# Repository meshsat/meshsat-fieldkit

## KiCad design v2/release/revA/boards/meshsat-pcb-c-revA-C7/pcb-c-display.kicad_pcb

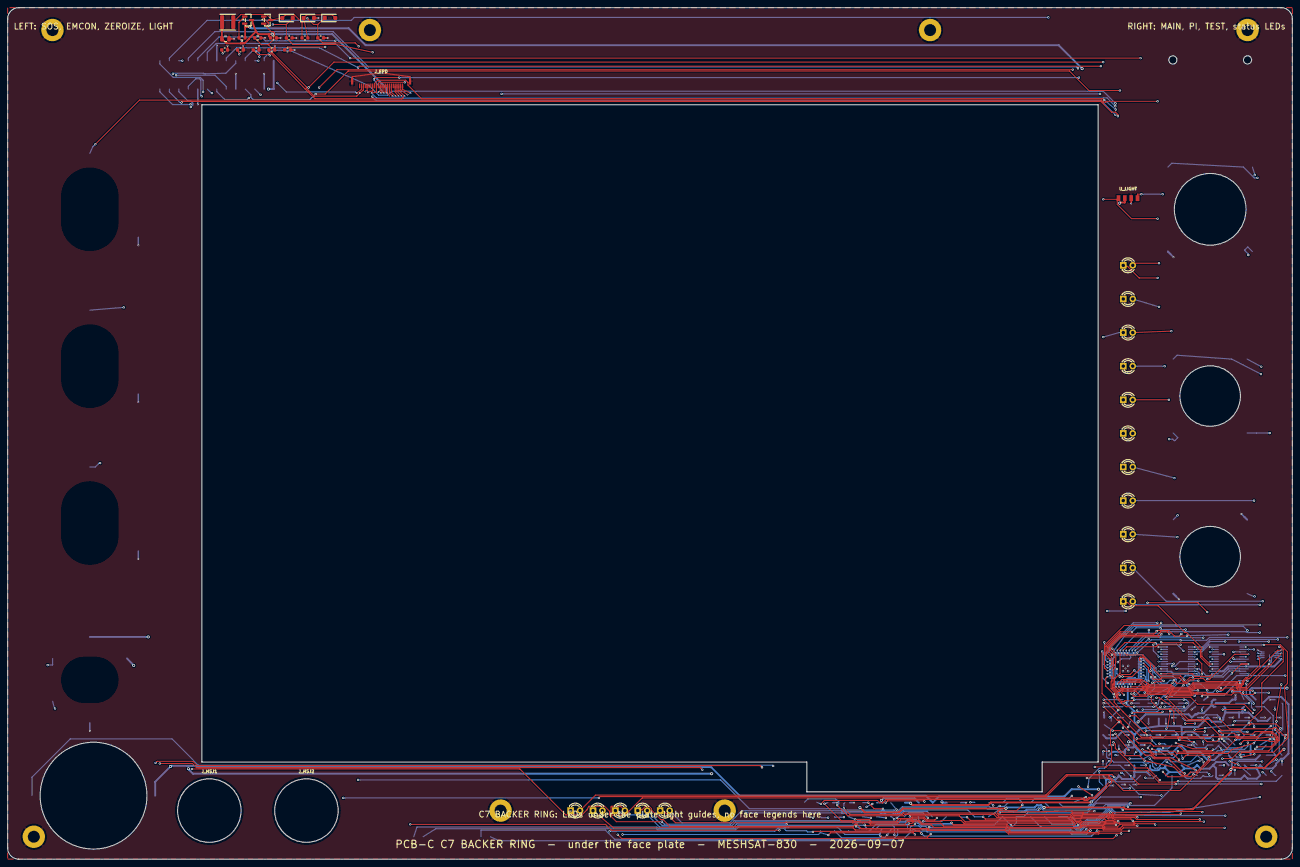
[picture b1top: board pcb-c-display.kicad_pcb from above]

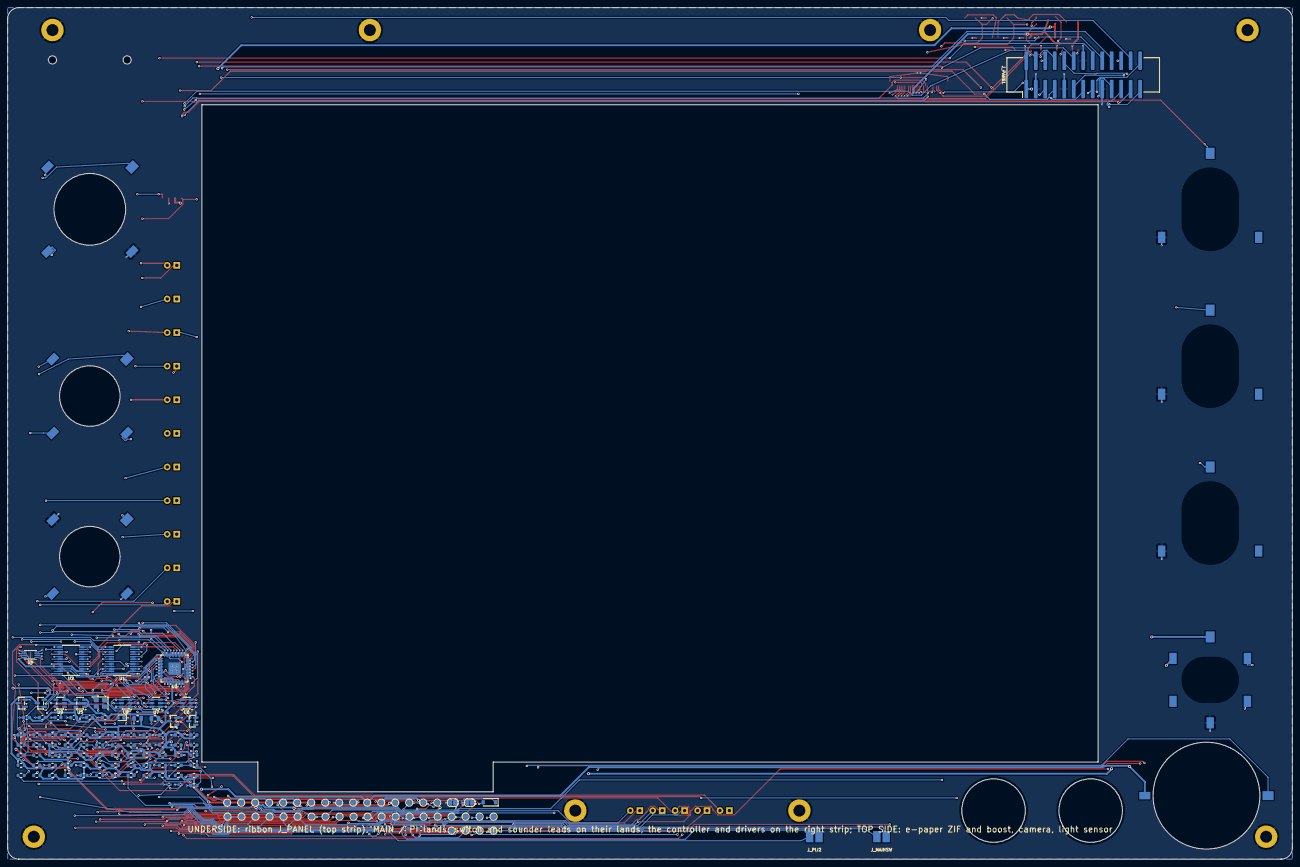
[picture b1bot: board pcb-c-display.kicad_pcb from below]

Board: 4 copper layers, 344.0 x 228.0 mm, 192 parts (136 on the bottom side), 133 nets.

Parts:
BZ1: IP67 panel-mount sounder, 5 V DC continuous, beze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; PanelSounder
C1, C2: 10u; C_0805_2012Metric
C3, C4, C14, C15, C16: 1u; C_0603_1608Metric
C5, C6: 15p NP0; C_0402_1005Metric
C7, C8, C9, C10, C11, C12, C13, C17, C18, C25, C26, C27, C29, C38: 100n; C_0603_1608Metric
C19, C20, C21, C22, C23, C24: 10n; C_0603_1608Metric
C28: 4.7u; C_0805_2012Metric
C30, C31, C32, C33, C34, C35, C36, C37: 1u 25V; C_0603_1608Metric
CAM_H1, CAM_H2: M2 screw of the USB camera module (25 x 25 board,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; MountingHole_2.2mm_M2
D1: 3 mm MWARN red, sunlight viewable; LED_D3.0mm
D2: 3 mm MCAUT amber, sunlight viewable; LED_D3.0mm
D3: 3 mm TX red (RF hazard), sunlight viewable; LED_D3.0mm
D4: 3 mm SOSACT red, sunlight viewable; LED_D3.0mm
D5: 3 mm SAT green, sunlight viewable; LED_D3.0mm
D6: 3 mm MESH green, sunlight viewable; LED_D3.0mm
D7: 3 mm LTE green, sunlight viewable; LED_D3.0mm
D8: 3 mm GPS green, sunlight viewable; LED_D3.0mm
D9: 3 mm SHORE green, sunlight viewable; LED_D3.0mm
D10: 3 mm CHG white, sunlight viewable; LED_D3.0mm
D11: 3 mm MSG white, sunlight viewable; LED_D3.0mm
D12: 3 mm BAT1 amber, sunlight viewable; LED_D3.0mm
D13: 3 mm BAT2 green, sunlight viewable; LED_D3.0mm
D14: 3 mm BAT3 green, sunlight viewable; LED_D3.0mm
D15: 3 mm BAT4 green, sunlight viewable; LED_D3.0mm
D16: 3 mm BAT5 green, sunlight viewable; LED_D3.0mm
D17: BAT54 lamp-test tie; D_SOD-123
D18: status (GPIO25); LED_0603_1608Metric
D19: SS2040FL: EPD_SW -> VGH; D_SOD-123F
D20: SS2040FL: pump clamp; D_SOD-123F
D21: SS2040FL: pump -> VGL; D_SOD-123F
FB1, FB2, FB3, FB4: ferrite 600R; L_0603_1608Metric
H1, H2, H3, H4, H5, H6, H7, H8: M3 x 6 into the face plate's self-clinching stand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; BackerScrew_M3_GND
JP1: BOOTSEL: short while powering to enter the USB bo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; SolderJumper-2_P1.3mm_Open_RoundedPad1.0x1.5mm
JP2: PANEL_ID strap (closed = variant B); SolderJumper-2_P1.3mm_Open_RoundedPad1.0x1.5mm
J_EPD: Hirose FH34SRJ-24S-0.5SH ZIF for the E2370KS0C1 f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; Hirose_FH34SRJ-24S
J_HSJ1: U-174/U headset jack 1 (Amphenol Nexus class, dra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; PanelJack_17mm
J_HSJ2: U-174/U headset jack 2 (Amphenol Nexus class, dra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; PanelJack_17mm
J_MAINSW: MAIN button lead to A22 J_MAINSW (XH2.5 at the A2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; LeadLands_1x02
J_PANEL: panel ribbon from B16 J_PANEL (IDC 2x13 SMD, unde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; IDC-Header_2x13_P2.54mm_Vertical_SMD
J_PIJ2: PI button lead: two solder lands on the underside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; LeadLands_1x02
L1: 10uH ATNR4010100MT 0.8 A (the boost inductor); L_APV_ANR4020
Q1: AO3401A P-FET high side; SOT-23
Q2, Q3, Q4: 2N7002; SOT-23
Q5: AO3401A P-FET: the e-paper's supply switch (EPD_P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; SOT-23
Q6: Si1308EDL class N-FET (RDS under 200 mOhm, VGS 2.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; SOT-23
R1, R6, R37: 1k; R_0603_1608Metric
R2, R3: 27R; R_0603_1608Metric
R4, R9, R10, R11, R12, R13, R15, R16, R42: 10k; R_0603_1608Metric
R5: 1k (BOOTSEL); R_0603_1608Metric
R7, R8, R17: 2.2k; R_0603_1608Metric
R14, R20, R38, R45: 100k; R_0603_1608Metric
R18: 47R; R_0603_1608Metric
R19, R44: 100R; R_0603_1608Metric
R21, R22, R23, R31, R36, R40: 300R; R_0603_1608Metric
R24, R25, R26, R27, R28, R29, R30, R32, R33, R34, R35: 180R; R_0603_1608Metric
R39, R41: 470R; R_0603_1608Metric
R43: 0.47R 1%; R_0603_1608Metric
SW_EMCON: EMCON locking toggle (closed = TX inhibit, a hard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; ToggleBody_SPDT
SW_LIGHT: LIGHTING DAY/NIGHT/BLACKOUT toggle DPDT ON-ON-ON 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; ToggleBody_DPDT
SW_MAIN: MAIN PWR 19 mm momentary, green ring (to A22 J_MA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; PanelSwitch_19mm
SW_PI: PI 16 mm recessed momentary, amber ring (PI_SHDN_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; PanelSwitch_16mm
SW_SOS: SOS locking toggle, maintained (APEM 5636ADKB-2V,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; ToggleBody_SPDT
SW_TEST: TEST/ACK 16 mm momentary, white ring; C&K ATP16-S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; PanelSwitch_16mm
SW_ZERO: ZEROIZE locking toggle, maintained (APEM 5636ADKB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; ToggleBody_SPDT
TP1: SWCLK; TestPoint_Pad_D1.5mm
TP2: SWDIO; TestPoint_Pad_D1.5mm
TP3: C_RUN; TestPoint_Pad_D1.5mm
TP4: LED_RAIL; TestPoint_Pad_D1.5mm
TP5: LED_RAIL_SW; TestPoint_Pad_D1.5mm
TP6: +5V; TestPoint_Pad_D1.5mm
TP7: +3V3; TestPoint_Pad_D1.5mm
TP8: GND; TestPoint_Pad_D1.5mm
TP9: EXP_INT; TestPoint_Pad_D1.5mm
TP10: TX_INHIBIT_n; TestPoint_Pad_D1.5mm
TP11: EMCON_HW; TestPoint_Pad_D1.5mm
TP12: ZEROIZE_HW; TestPoint_Pad_D1.5mm
TP13: SPARE1; TestPoint_Pad_D1.5mm
TP14: SPARE2; TestPoint_Pad_D1.5mm
TP15: SPARE3; TestPoint_Pad_D1.5mm
TP16: SPARE4; TestPoint_Pad_D1.5mm
TP17: SPARE5; TestPoint_Pad_D1.5mm
TP18: SPARE6; TestPoint_Pad_D1.5mm
TP19: SPARE7; TestPoint_Pad_D1.5mm
TP20: SPARE8; TestPoint_Pad_D1.5mm
TP21: SPARE9; TestPoint_Pad_D1.5mm
TP22: SPARE10; TestPoint_Pad_D1.5mm
TP23: SPARE11; TestPoint_Pad_D1.5mm
TP24: SPARE12; TestPoint_Pad_D1.5mm
TP25: EPD_BUSY; TestPoint_Pad_D1.5mm
TP26: EPD_VGH; TestPoint_Pad_D1.5mm
TP27: EPD_VGL; TestPoint_Pad_D1.5mm
TP28: HB1; TestPoint_Pad_D1.5mm
TP29: HB2; TestPoint_Pad_D1.5mm
TP30: HB3; TestPoint_Pad_D1.5mm
TP31: SLOT_EN1; TestPoint_Pad_D1.5mm
TP32: SLOT_EN2; TestPoint_Pad_D1.5mm
TP33: SLOT_EN3; TestPoint_Pad_D1.5mm
TP34: HDMI_SEL1; TestPoint_Pad_D1.5mm
TP35: HDMI_SEL2; TestPoint_Pad_D1.5mm
TP36: PI_SHDN_REQ; TestPoint_Pad_D1.5mm
TP37: PI_KILL; TestPoint_Pad_D1.5mm
TP38: SHORE_INHIBIT; TestPoint_Pad_D1.5mm
TP39: PIJ2_A; TestPoint_Pad_D1.5mm
TP40: PIJ2_B; TestPoint_Pad_D1.5mm
U1: PCA9555PW 0x22: LED sinks, light mode inputs; TSSOP-24_4.4x7.8mm_P0.65mm
U2: PCA9555PW 0x23: LED sinks, the battery bar, lamp 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; TSSOP-24_4.4x7.8mm_P0.65mm
U3: RP2040 panel controller (USB device on B16's slot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; QFN-56-1EP_7x7mm_P0.4mm_EP3.2x3.2mm
U4: W25Q16JVUXIQ 16 Mbit QSPI flash (USON-8: 1 CS 2 D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; Winbond_USON-8-1EP_3x2mm_P0.5mm_EP0.2x1.6mm
U5: TLV75533PDBV 3.3 V 500 mA LDO for the controller,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; SOT-23-5
U6, U7, U8: USBLC6-2SC6; SOT-23-6
U9: 74LVC1G04 inverter (2 A 4 Y): EMCON_HW = NOT TX_I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; SOT-23-5
U_LIGHT: Vishay VEML7700 ambient light sensor (1 SCL 2 VDD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; Vishay_VEML7700
Y1: 12 MHz ABM8-272-T3 (3225): 1 XIN, 3 XOUT, 2 and 4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; Crystal_SMD_3225-4Pin_3.2x2.5mm

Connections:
/+3V3: C2.1, C4.1, C7.1, C8.1, C9.1, C10.1, C11.1, C12.1, C13.1, C16.1, C17.1, C18.1, C25.1, C38.1, Q5.2, R4.2, R7.2, R8.2, R9.2, R10.2, R11.2, R12.2, R13.2, R14.2, R16.2, R42.2, TP7.1, U1.2, U1.24, U2.2, U2.21, U2.24, U3.1, U3.10, U3.22, U3.33, U3.42, U3.43, U3.44, U3.48, U3.49, U4.8, U5.5, U6.5, U7.5, U8.5, U9.5, U_LIGHT.2
/+5V: BZ1.2, C1.1, C3.1, J_PANEL.1, J_PANEL.2, SW_LIGHT.2, TP6.1, U5.1, U5.3
/BAT1_A: D12.2, R31.2
/BAT1_K: D12.1, U2.7
/BAT2_A: D13.2, R32.2
/BAT2_K: D13.1, U2.8
/BAT3_A: D14.2, R33.2
/BAT3_K: D14.1, U2.9
/BAT4_A: D15.2, R34.2
/BAT4_K: D15.1, U2.10
/BAT5_A: D16.2, R35.2
/BAT5_K: D16.1, U2.11
/BOOT_J: JP1.1, R5.2
/BZ_K: BZ1.1, Q4.3
/CHG_A: D10.2, R29.2
/CHG_K: D10.1, U1.7
/C_DVDD: C14.1, C15.1, U3.23, U3.45, U3.50
/C_RUN: R4.1, TP3.1, U3.26
/EMCON_HW: J_PANEL.8, TP11.1, U3.32, U9.4
/EPD_BUSY: J_EPD.9, TP25.1, U3.9
/EPD_CS: J_EPD.12, U3.7
/EPD_DC: J_EPD.11, U3.6
/EPD_GDR: J_EPD.2, Q6.1
/EPD_PUMP: C31.2, D20.1, D21.2
/EPD_PWR_n: Q5.1, R42.1, U3.41
/EPD_RESE: J_EPD.3, Q6.2, R43.1
/EPD_RST: J_EPD.10, U3.8
/EPD_SCL: J_EPD.13, U3.4
/EPD_SDA: J_EPD.14, U3.5
/EPD_SW: C31.1, D19.1, L1.2, Q6.3
/EPD_VCC: C28.1, C29.1, J_EPD.15, J_EPD.16, L1.1, Q5.3
/EPD_VCOM: C37.1, J_EPD.24
/EPD_VDDD: C34.1, J_EPD.18
/EPD_VDH: C35.1, J_EPD.20
/EPD_VDHR: C33.1, J_EPD.5
/EPD_VDL: C36.1, J_EPD.22
/EPD_VGH: C30.1, D19.2, J_EPD.21, TP26.1
/EPD_VGL: C32.1, D21.1, J_EPD.23, TP27.1
/EXP_INT: J_PANEL.6, TP9.1, U1.1, U2.1, U3.36, U8.3, U8.4
/GPS_A: D8.2, R27.2
/GPS_K: D8.1, U1.11
/HB1: J_PANEL.18, TP28.1, U3.13
/HB2: J_PANEL.19, TP29.1, U3.14
/HB3: J_PANEL.20, TP30.1, U3.15
/HDMI_SEL1: J_PANEL.12, TP34.1, U3.27
/HDMI_SEL2: J_PANEL.13, TP35.1, U3.28
/LED_RAIL: Q1.3, R21.1, R22.1, R23.1, R24.1, R25.1, R26.1, R27.1, R28.1, R29.1, R30.1, R31.1, R32.1, R33.1, R34.1, R35.1, R36.1, R40.1, R41.1, TP4.1
/LED_RAIL_SW: Q1.2, R15.1, R17.1, R39.1, SW_LIGHT.1, TP5.1
/LED_STAT: R6.1, U3.37
/LED_STAT_A: D18.2, R6.2
/LIGHT_DAY_n: C22.1, R12.1, SW_LIGHT.5, U1.13
/LIGHT_NIGHT_n: C23.1, R13.1, SW_LIGHT.6, U1.14
/LTE_A: D7.2, R26.2
/LTE_K: D7.1, U1.10
/MAINRING_A: R39.2, SW_MAIN.3
/MAINSW_A: FB1.1, SW_MAIN.1
/MAINSW_A2: C26.1, FB1.2, J_MAINSW.1
/MAINSW_B: FB2.1, SW_MAIN.2
/MAINSW_B2: C26.2, FB2.2, J_MAINSW.2
/MCAUT_A: D2.2, R22.2
/MCAUT_K: D2.1, U1.6
/MESH_A: D6.2, R25.2
/MESH_K: D6.1, U1.9
/MSG_A: D11.2, R30.2
/MSG_K: D11.1, U2.5
/MWARN_A: D1.2, R21.2
/MWARN_K: D1.1, U1.5
/PANEL_ID: JP2.1, R16.1, U1.15
/PANEL_PWM: R19.1, U3.11
/PIJ2_A: FB3.1, SW_PI.1, TP39.1
/PIJ2_A2: C27.1, FB3.2, J_PIJ2.1
/PIJ2_B: FB4.1, SW_PI.2, TP40.1
/PIJ2_B2: C27.2, FB4.2, J_PIJ2.2
/PIRING_A: R40.2, SW_PI.3
/PIRING_K: SW_PI.4, U2.6
/PI_KILL: J_PANEL.25, TP37.1, U3.30
/PI_SHDN_REQ: J_PANEL.24, TP36.1, U3.29
/PWM1: R44.1, U3.12
/Q1_G: Q1.1, R17.2, R18.1
/Q2_D: Q2.3, R18.2
/Q2_G: Q2.1, R19.2, R20.1
/Q3_G: Q3.1, R37.2, R38.1
/Q4_G: Q4.1, R44.2, R45.1
/QSPI_D0: U3.53, U4.5
/QSPI_D1: U3.55, U4.2
/QSPI_D2: U3.54, U4.3
/QSPI_D3: U3.51, U4.7
/QSPI_SCLK: U3.52, U4.6
/QSPI_SS: R5.1, U3.56, U4.1
/RAIL_SENSE: R15.2, U3.38
/SAT_A: D5.2, R24.2
/SAT_K: D5.1, U1.8
/SCL: J_PANEL.5, R8.1, U1.22, U2.22, U3.3, U7.3, U7.4, U_LIGHT.1
/SDA: J_PANEL.4, R7.1, U1.23, U2.23, U3.2, U7.1, U7.6, U_LIGHT.4
/SHORE_A: D9.2, R28.2
/SHORE_INHIBIT: J_PANEL.26, TP38.1, U3.31
/SHORE_K: D9.1, U2.4
/SLOT_EN1: J_PANEL.21, TP31.1, U3.16
/SLOT_EN2: J_PANEL.22, TP32.1, U3.17
/SLOT_EN3: J_PANEL.23, TP33.1, U3.18
/SOSACT_A: D4.2, R23.2
/SOSACT_K: D4.1, U1.4
/SOS_SW: C19.1, R9.1, SW_SOS.1, U3.40
/SPARE1: TP13.1, U1.16
/SPARE2: TP14.1, U1.17
/SPARE3: TP15.1, U1.18
/SPARE4: TP16.1, U1.19
/SPARE5: TP17.1, U1.20
/SPARE6: TP18.1, U2.14
/SPARE7: TP19.1, U2.15
/SPARE8: TP20.1, U2.16
/SPARE9: TP21.1, U2.17
/SPARE10: TP22.1, U2.18
/SPARE11: TP23.1, U2.19
/SPARE12: TP24.1, U2.20
/SWCLK: TP1.1, U3.24
/SWDIO: TP2.1, U3.25
/TESTRING_A: R41.2, SW_TEST.3
/TEST_SW: C21.1, R11.1, SW_TEST.1, U3.39
/TR_APRS: J_PANEL.7, R37.1, U3.35, U8.1, U8.6
/TX_A: D3.2, R36.2
/TX_INHIBIT_n: C24.1, J_PANEL.11, R14.1, SW_EMCON.1, TP10.1, U9.2
/TX_K: D3.1, D17.2, Q3.3
/TX_LAMPTEST: D17.1, U2.13
/USB_DM_R: R3.1, U3.46
/USB_DP_R: R2.1, U3.47
/USB_PNL_N: J_PANEL.16, R3.2, U6.3, U6.4
/USB_PNL_P: J_PANEL.15, R2.2, U6.1, U6.6
/XIN: C5.1, U3.20, Y1.1
/XOUT: C6.1, R1.2, Y1.3
/XOUT_R: R1.1, U3.21
/ZEROIZE_HW: C20.1, J_PANEL.10, R10.1, SW_ZERO.1, TP12.1, U3.34
GND: C1.2, C2.2, C3.2, C4.2, C5.2, C6.2, C7.2, C8.2, C9.2, C10.2, C11.2, C12.2, C13.2, C14.2, C15.2, C16.2, C17.2, C18.2, C19.2, C20.2, C21.2, C22.2, C23.2, C24.2, C25.2, C28.2, C29.2, C30.2, C32.2, C33.2, C34.2, C35.2, C36.2, C37.2, C38.2, D18.1, D20.2, H1.1, H2.1, H3.1, H4.1, H5.1, H6.1, H7.1, H8.1, JP1.2, JP2.2, J_EPD.8, J_EPD.17, J_EPD.25, J_EPD.26, J_PANEL.3, J_PANEL.9, J_PANEL.14, J_PANEL.17, Q2.2, Q3.2, Q4.2, R20.2, R38.2, R43.2, R45.2, SW_EMCON.2, SW_LIGHT.4, SW_MAIN.4, SW_SOS.2, SW_TEST.2, SW_TEST.4, SW_ZERO.2, TP8.1, U1.3, U1.12, U1.21, U2.3, U2.12, U3.19, U3.57, U4.4, U4.9, U5.2, U6.2, U7.2, U8.2, U9.3, U_LIGHT.3, Y1.2, Y1.4

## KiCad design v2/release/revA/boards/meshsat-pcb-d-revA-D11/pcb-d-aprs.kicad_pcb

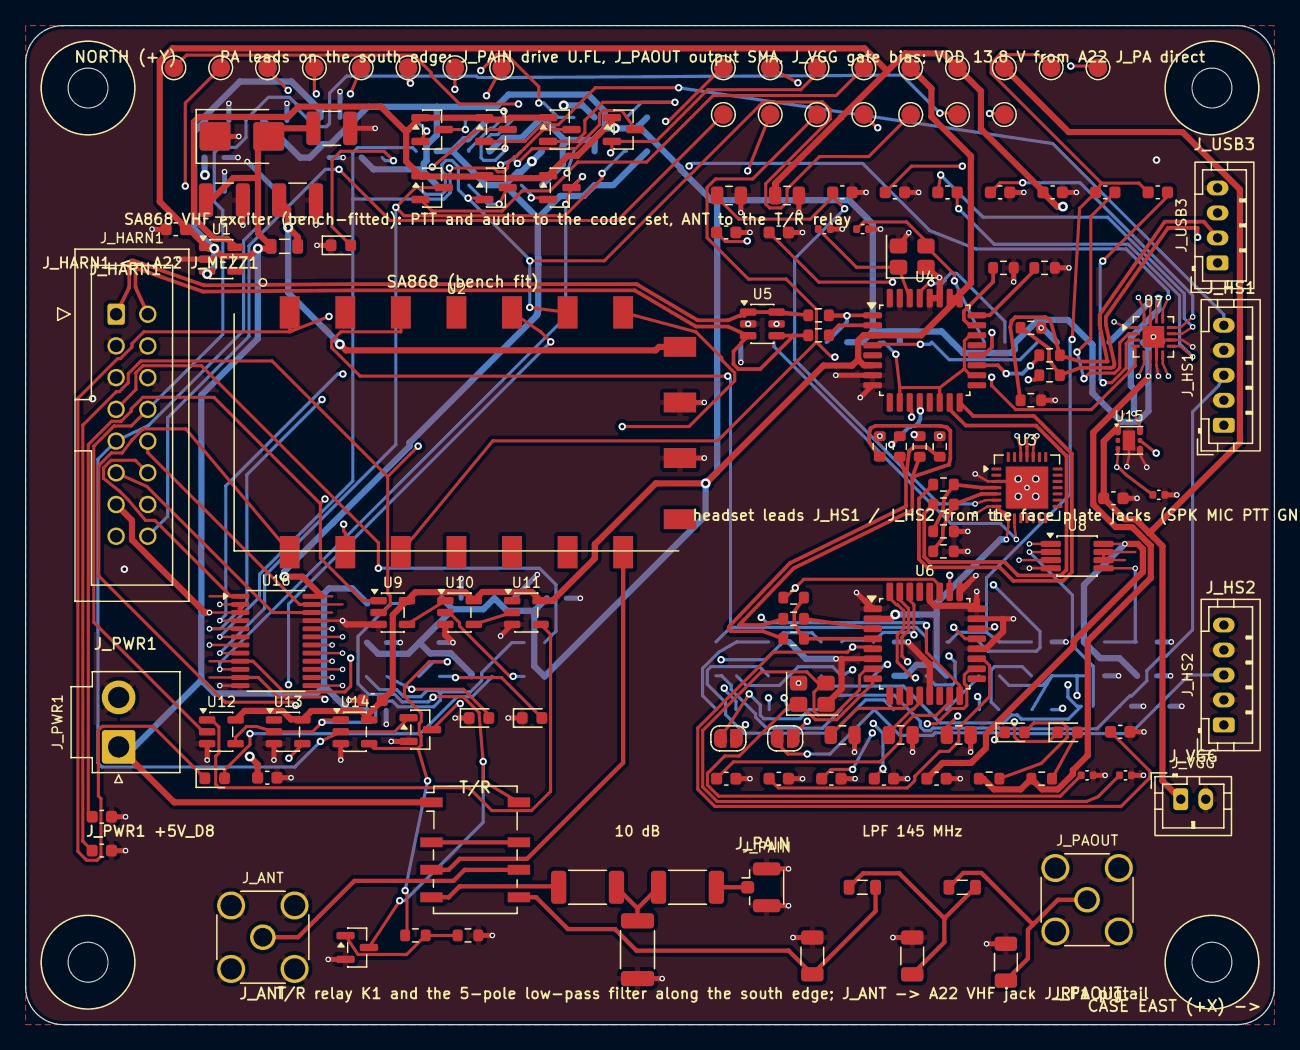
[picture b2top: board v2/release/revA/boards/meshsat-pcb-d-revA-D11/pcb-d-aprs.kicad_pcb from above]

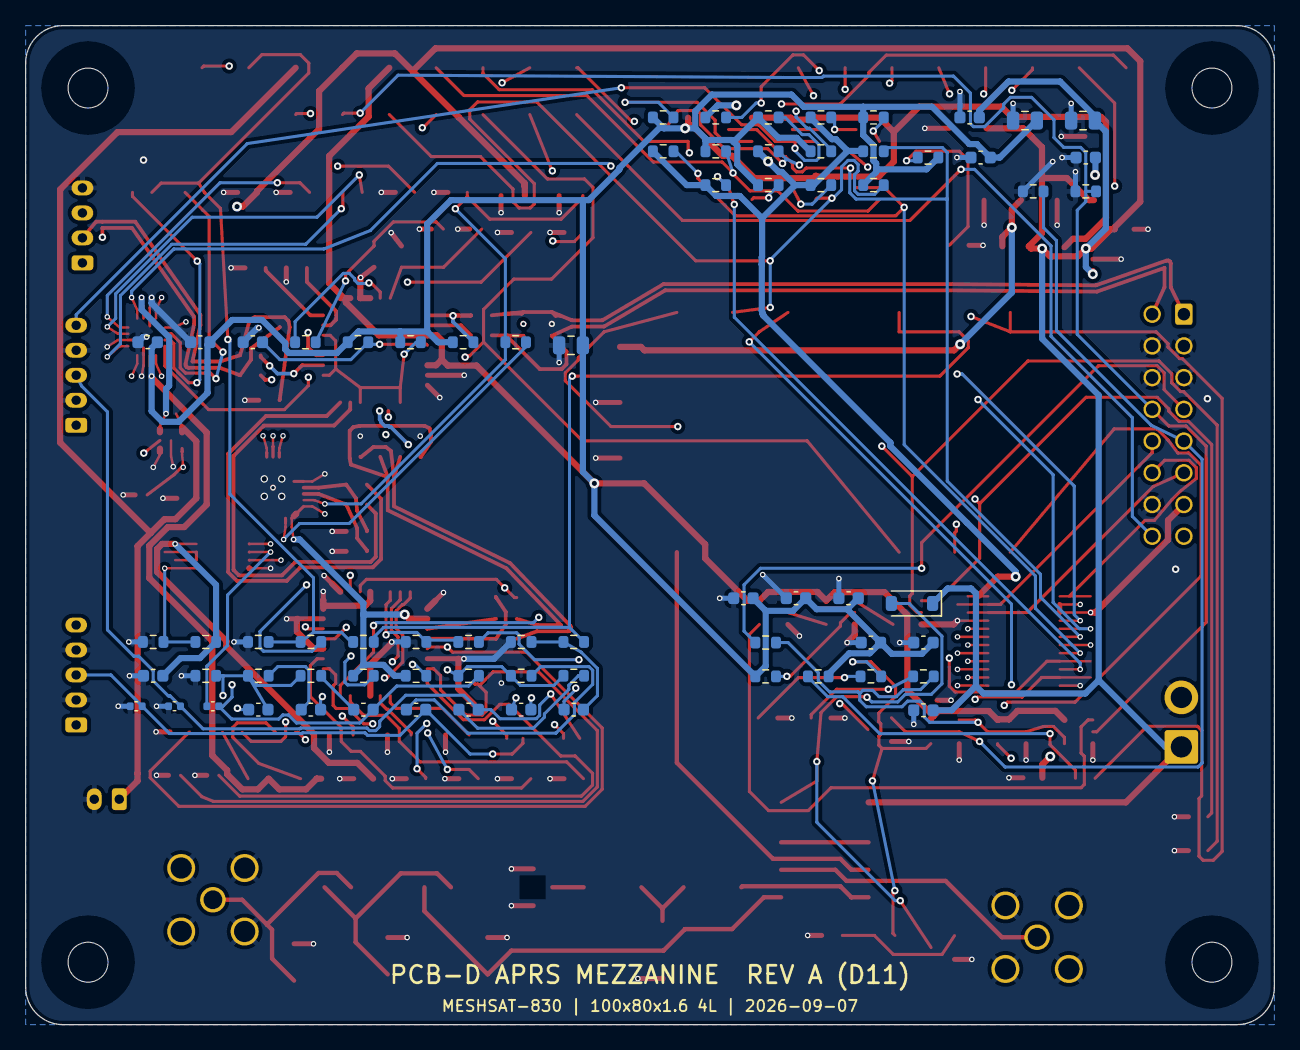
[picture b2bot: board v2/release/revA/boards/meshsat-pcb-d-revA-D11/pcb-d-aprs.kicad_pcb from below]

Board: 4 copper layers, 100.0 x 80.0 mm, 211 parts (71 on the bottom side), 133 nets.

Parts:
C1, C2, C5: 47u 6.3V X5R 1210; C_1210_3225Metric
C3, C9, C17, C24, C25, C33, C40: 10u; C_0805_2012Metric
C4, C6, C11, C15, C16, C39, C49, C50, C51, C52, C53, C54, C55, C56, C57, C62, C63: 100n; C_0603_1608Metric
C7, C8, C12, C18, C19, C20, C21, C22, C23, C28, C29, C30, C31, C32, C34, C35, C36, C37, C38, C41, C42, C46, C47, C48: 1u; C_0603_1608Metric
C10: 4.7u; C_0805_2012Metric
C13, C14: 27p NP0; C_0402_1005Metric
C26, C27: 18p NP0; C_0402_1005Metric
C43: 100p NP0; C_0402_1005Metric
C44, C45: 1n NP0; C_0402_1005Metric
C58, C60: 22p 500V NP0 1206; C_1206_3216Metric
C59: 39p 500V NP0 1206; C_1206_3216Metric
C61: 4.7n; C_0402_1005Metric
D1: SMBJ5.0A; D_SMB
D2: 1N4148W coil flyback; D_SOD-123
FB1: 600R 2A ferrite (the exciter's 1 A transmit pulse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; L_0805_2012Metric
H1, H2, H3, H4: M3 standoff on A22 (5/95, +-35); MountingHole_3.2mm_M3
JP1: electret bias headset 1 (close for an electret mi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; SolderJumper-2_P1.3mm_Open_RoundedPad1.0x1.5mm
JP2: electret bias headset 2; SolderJumper-2_P1.3mm_Open_RoundedPad1.0x1.5mm
J_ANT: SMA jack: antenna pigtail to A22's VHF jack J_RF1; SMA_Amphenol_132134_Vertical
J_HARN1: A22 mezzanine harness J_MEZZ1 (IDC 2x8): USB pair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; IDC-Header_2x08_P2.54mm_Vertical_NarrowPad
J_HS1: JST-PH 1x5 socket: headset 1, SPK GND MIC GND PTT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; JST_PH_B5B-PH-K_1x05_P2.00mm_Vertical
J_HS2: JST-PH 1x5 socket: headset 2, SPK GND MIC GND PTT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; JST_PH_B5B-PH-K_1x05_P2.00mm_Vertical
J_PAIN: U.FL socket: PA drive (coax to the RA30H1317M1 in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; U.FL_Hirose_U.FL-R-SMT-1_Vertical
J_PAOUT: SMA jack: PA output (coax from the RA30H1317M1 ou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; SMA_Amphenol_132134_Vertical
J_PWR1: JST-VH socket, 10 A: 5 V from A22 J_MEZZ_PWR1 (be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; JST_VH_B2P-VH_1x02_P3.96mm_Vertical
J_USB3: JST-PH 1x4 socket: spare hub port 3, 5V D- D+ GND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; JST_PH_B4B-PH-K_1x04_P2.00mm_Vertical
J_VGG: JST-PH 1x2 socket: PA gate bias, VGG GND (the lea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; JST_PH_B2B-PH-K_1x02_P2.00mm_Vertical
K1: Omron G6K-2F-Y 5 VDC DPDT signal relay, T/R; Relay_DPDT_Omron_G6K-2F-Y
L1: 68nH 0805 (LPF, 145 MHz 5th order; values to be v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; L_0805_2012Metric
L2: 68nH 0805 (LPF); L_0805_2012Metric
LED1: green power; LED_0603_1608Metric
LED2: amber record; LED_0603_1608Metric
LED3: green playback; LED_0603_1608Metric
LED4: red transmit; LED_0603_1608Metric
LED5: amber PA keyed; LED_0603_1608Metric
LED6: green receive (AUDIO_ON low); LED_0603_1608Metric
Q1: 2N7002 PA_EN -> H/L low (never tie H/L high); SOT-23
Q2: 2N7002 relay coil; SOT-23
Q3, Q4, Q5, Q6, Q7, Q8, Q9: 2N7002; SOT-23
R1, R43, R44, R51: 2.2k; R_0603_1608Metric
R2, R3, R34, R53: 100k; R_0603_1608Metric
R4, R29, R30, R49, R50, R52: 1k; R_0603_1608Metric
R5, R9, R10, R31, R32, R35, R36, R37, R38, R39, R45, R46, R47, R66, R67, R68, R69, R70, R71, R72, R73, R74, R75, R76, R77, R78, R79: 10k; R_0603_1608Metric
R6, R7, R12, R13, R16, R17, R20, R21: 22; R_0603_1608Metric
R8, R11, R28: 1.5k; R_0603_1608Metric
R14, R15, R18, R19, R22, R23, R24, R25: 15k; R_0603_1608Metric
R26, R27: 33; R_0603_1608Metric
R33, R40, R41: 4.7k; R_0603_1608Metric
R42: 220k; R_0603_1608Metric
R48: 100; R_0603_1608Metric
R54, R56: 27 1% 2010; R_2010_5025Metric
R55: 36 1% 2010; R_2010_5025Metric
TP1: AF_OUT; TestPoint_Pad_D1.5mm
TP2: MIC_SUM; TestPoint_Pad_D1.5mm
TP3: KEY; TestPoint_Pad_D1.5mm
TP4: PA_KEY; TestPoint_Pad_D1.5mm
TP5: +3V3_D8; TestPoint_Pad_D1.5mm
TP6: +5V_D8; TestPoint_Pad_D1.5mm
TP7: VGG_SW; TestPoint_Pad_D1.5mm
TP8: RX_MIX; TestPoint_Pad_D1.5mm
TP9: ZEROIZE_HW; TestPoint_Pad_D1.5mm
TP10: AB_SPARE; TestPoint_Pad_D1.5mm
TP11: SA_TXD; TestPoint_Pad_D1.5mm
TP12: SA_RXD; TestPoint_Pad_D1.5mm
TP13: PTT_SW_n; TestPoint_Pad_D1.5mm
TP14: SA_PD; TestPoint_Pad_D1.5mm
TP15: TX_INHIBIT_n; TestPoint_Pad_D1.5mm
TP16: PA_EN; TestPoint_Pad_D1.5mm
TP17: EXP_SPARE1; TestPoint_Pad_D1.5mm
TP18: EXP_SPARE2; TestPoint_Pad_D1.5mm
TP19: EXP_SPARE3; TestPoint_Pad_D1.5mm
TP20: EXP_SPARE4; TestPoint_Pad_D1.5mm
TP21: EXP_SPARE5; TestPoint_Pad_D1.5mm
TP22: EXP_SPARE6; TestPoint_Pad_D1.5mm
TP23: EXP_SPARE7; TestPoint_Pad_D1.5mm
TP24: EXP_SPARE8; TestPoint_Pad_D1.5mm
U1: TLV75533PDBV 3.3 V 500 mA LDO (1 IN 2 GND 3 EN 4 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; SOT-23-5
U2: NiceRF SA868 VHF 2 W exciter, bench-fitted (caste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; NiceRF_SA868
U3: CP2102N-A02-GQFN28 USB-UART bridge (SAU); QFN-28-1EP_5x5mm_P0.5mm_EP3.35x3.35mm
U4: TUSB2046BI four-port USB 2.0 full-speed hub (LQFP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; LQFP-32_7x7mm_P0.8mm
U5: USBLC6-2SC6; SOT-23-6
U6: TI PCM2912A USB audio codec (TQFP-32): mono input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; TQFP-32_7x7mm_P0.8mm
U7: TI TPA6132A2 headphone amplifier (QFN-16), receiv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; QFN-16-1EP_3x3mm_P0.5mm_EP1.75x1.75mm
U8: TLV9062IDGK dual op amp (1 OUT1 2 IN1- 3 IN1+ 4 V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; VSSOP-8_3x3mm_P0.65mm
U9: 74LVC1G08 AND (1 A 2 B 3 GND 4 Y 5 VCC): both hea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; SOT-23-5
U10: 74LVC1G08 AND: headsets AND software PTT (RTS); SOT-23-5
U11: 74LVC1G04 inverter (2 A 4 Y): PTT_ANY; SOT-23-5
U12: 74LVC1G08 AND: KEY = PTT_ANY AND TX_INHIBIT_n (th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; SOT-23-5
U13: 74LVC1G04 inverter: KEY -> SA868 PTT (low = trans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; SOT-23-5
U14: 74LVC1G08 AND: PA_KEY = KEY AND PA_EN (A22's PA r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; SOT-23-5
U15: TPS22810DRV; WSON-6-1EP_2x2mm_P0.65mm_EP1x1.6mm
U16: PCA9555PW 0x26: COS, PTT states, KEY, PA_KEY in; 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; TSSOP-24_4.4x7.8mm_P0.65mm
Y1: 6 MHz 3225 (CL 20 pF; C1 = C2 = 27 pF and Rd 1.5k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; Crystal_SMD_3225-4Pin_3.2x2.5mm
Y2: 6 MHz 3225 (codec clock; 18 pF loads, to confirm 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; Crystal_SMD_3225-4Pin_3.2x2.5mm

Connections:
/+3V3: C63.1, J_HARN1.13, R67.2, R69.2, R71.2, R73.2, R75.2, R77.2, R79.2, U16.2, U16.3, U16.24
/+3V3_D8: C8.1, C9.1, C15.1, C16.1, C17.1, C51.1, C52.1, C53.1, C54.1, C55.1, C56.1, Q3.1, Q4.1, Q5.1, Q6.1, Q7.1, Q8.1, Q9.1, R1.1, R5.2, R8.2, R9.2, R10.2, R29.1, R30.1, R51.1, R66.2, R68.2, R70.2, R72.2, R74.2, R76.2, R78.2, TP5.1, U1.5, U4.3, U4.6, U4.25, U4.26, U7.6, U9.5, U10.5, U11.5, U12.5, U13.5, U14.5
/+5V_D8: C1.1, C2.1, C3.1, C4.1, C7.1, C18.1, C32.1, C33.1, C39.1, C57.1, D1.2, D2.1, FB1.1, J_PWR1.1, J_USB3.1, K1.1, R38.1, R43.2, R44.2, TP6.1, U1.1, U1.3, U3.7, U3.8, U5.5, U6.2, U7.14, U8.8, U15.6
/+5V_SA: C5.1, C6.1, FB1.2, U2.8
/AB_SPARE: J_HARN1.16, TP10.1
/AF_DIV: C28.1, R31.2, R32.1
/AF_OUT: R31.1, R35.1, TP1.1, U2.3
/AMP_CPN: C30.2, U7.9
/AMP_CPP: C30.1, U7.11
/AMP_EN: Q9.2, R78.1, U7.13
/AMP_HPVDD: C31.1, U7.12
/AMP_HPVSS: C29.1, U7.8
/AMP_INL_N: C37.1, U7.1
/AMP_INL_P: C35.2, U7.2
/AMP_INR_N: C38.1, U7.4
/AMP_INR_P: C36.2, U7.3
/EXP_INT: J_HARN1.12, U16.1
/EXP_SPARE1: TP17.1, U16.13
/EXP_SPARE2: TP18.1, U16.14
/EXP_SPARE3: TP19.1, U16.15
/EXP_SPARE4: TP20.1, U16.16
/EXP_SPARE5: TP21.1, U16.17
/EXP_SPARE6: TP22.1, U16.18
/EXP_SPARE7: TP23.1, U16.19
/EXP_SPARE8: TP24.1, U16.20
/HS1_BIAS_R: JP1.2, R43.1
/HS1_MIC: C41.1, C44.1, JP1.1, J_HS1.3
/HS1_MIC_AC: C41.2, R40.1
/HS1_SPK: J_HS1.1, U7.16
/HS2_BIAS_R: JP2.2, R44.1
/HS2_MIC: C42.1, C45.1, JP2.1, J_HS2.3
/HS2_MIC_AC: C42.2, R41.1
/HS2_SPK: J_HS2.1, U7.5
/HUB_DM0: R7.2, U4.2
/HUB_DM1: R13.1, U4.11
/HUB_DM2: R17.1, U4.15
/HUB_DM3: R21.1, U4.19
/HUB_DM4: R25.1, U4.23
/HUB_DP0: R6.2, R8.1, U4.1
/HUB_DP1: R12.1, U4.12
/HUB_DP2: R16.1, U4.16
/HUB_DP3: R20.1, U4.20
/HUB_DP4: R24.1, U4.24
/HUB_OVRCUR_n: R9.1, U4.10, U4.14, U4.18, U4.22
/HUB_RST_n: C12.1, R10.1, U4.4
/HUB_XTAL1: C13.1, U4.30, Y1.1
/HUB_XTAL2: R11.2, U4.29
/HUB_XTAL2R: C14.1, R11.1, Y1.3
/KEY: Q6.2, R48.1, R49.1, R72.1, TP3.1, U12.4, U13.2, U14.1
/LED_PA_A: LED5.2, R50.2
/LED_PLAY_A: LED3.2, R30.2
/LED_PLAY_K: LED3.1, U6.32
/LED_PWR_A: LED1.2, R1.2
/LED_REC_A: LED2.2, R29.2
/LED_REC_K: LED2.1, U6.31
/LED_RX_A: LED6.2, R51.2
/LED_TX_A: LED4.2, R49.2
/MICAMP_AC: C46.2, R45.1
/MICAMP_IN_N: C43.2, R40.2, R41.2, R42.2, U8.2
/MICAMP_OUT: C43.1, C46.1, R42.1, U8.1
/MIC_IN: C48.2, U2.18
/MIC_SUM: C48.1, R45.2, R46.2, R47.1, TP2.1
/MMUTE: R33.2, R34.1, U6.30
/OPB_OUT: U8.6, U8.7
/PA_EN: J_HARN1.9, Q1.1, R3.1, TP16.1, U14.2
/PA_KEY: Q7.2, R50.1, R52.1, R74.1, TP4.1, U14.4, U15.5
/PCM_L_AC: C34.2, R36.1
/PCM_R_AC: C47.2, R46.1
/PCM_VCCA: C20.1, U6.15
/PCM_VCCL: C21.1, U6.19
/PCM_VCCP: C23.1, U6.26
/PCM_VCCR: C22.1, U6.21
/PCM_VCOM1: C24.1, U6.11
/PCM_VCOM2: C25.1, U6.12
/PCM_VDD: C19.1, R28.2, U6.5, U6.27
/PCM_VIN: C28.2, U6.16
/PCM_VOUTL: C34.1, U6.18
/PCM_VOUTR: C47.1, U6.22
/PCM_XTI: C26.1, U6.8, Y2.1
/PCM_XTO: C27.1, U6.7, Y2.3
/PTT_ANY: U11.4, U12.1
/PTT_ANY_n: U10.4, U11.2
/PTT_HS1_n: C49.1, J_HS1.5, Q4.2, R68.1, U9.1
/PTT_HS2_n: C50.1, J_HS2.5, Q5.2, R70.1, U9.2
/PTT_HS_n: U9.4, U10.1
/PTT_SW_n: R5.1, TP13.1, U3.24, U10.2
/RF_ANT: J_ANT.1, K1.6
/RF_DRV: J_PAIN.1, R56.2
/RF_LPF_M: C59.1, L1.2, L2.1
/RF_LPF_OUT: C60.1, K1.5, L2.2
/RF_PAD_IN: K1.4, R54.1
/RF_PAD_M: R54.2, R55.1, R56.1
/RF_PAOUT: C58.1, J_PAOUT.1, L1.1
/RF_RX: K1.2, K1.7
/RF_SA: K1.3, U2.12
/RLY_DRV: Q2.1, R52.2, R53.1
/RLY_K: D2.2, K1.8, Q2.3
/RX_MIX: C35.1, C36.1, R35.2, R36.2, R37.1, TP8.1
/SAU_3V3: C10.1, C11.1, R4.2, U3.6
/SAU_RST: R4.1, U3.9
/SA_AUDIO_ON_n: LED6.1, Q3.2, R66.1, U2.1
/SA_HL: Q1.3, U2.7
/SA_PD: Q8.2, R76.1, TP14.1, U2.6
/SA_PTT_n: U2.5, U13.4
/SA_RXD: TP12.1, U2.16, U3.26
/SA_TXD: TP11.1, U2.17, U3.25
/SCL: J_HARN1.11, U16.22
/SDA: J_HARN1.10, U16.23
/TR_APRS: J_HARN1.7, R48.2
/TX_INHIBIT_n: J_HARN1.8, R2.1, TP15.1, U12.2
/USB1_N: R13.2, R15.1, R27.1
/USB1_NR: R27.2, U6.3
/USB1_P: R12.2, R14.1, R26.1
/USB1_PR: R26.2, R28.1, U6.4
/USB2_N: R17.2, R19.1, U3.5
/USB2_P: R16.2, R18.1, U3.4
/USB3_N: J_USB3.2, R21.2, R23.1
/USB3_P: J_USB3.3, R20.2, R22.1
/USB_D8_N: J_HARN1.2, R7.1, U5.3, U5.4
/USB_D8_P: J_HARN1.1, R6.1, U5.1, U5.6
/VGG_CT: C61.1, U15.3
/VGG_SW: C62.1, J_VGG.1, TP7.1, U15.1
/VREF: C40.1, R38.2, R39.1, U8.3, U8.5
/X_AMP_EN: Q9.3, R79.1, U16.10
/X_COS_n: Q3.3, R67.1, U16.4
/X_KEY: Q6.3, R73.1, U16.7
/X_MMUTE: R33.1, U16.11
/X_PA_KEY: Q7.3, R75.1, U16.8
/X_PTT_HS1_n: Q4.3, R69.1, U16.5
/X_PTT_HS2_n: Q5.3, R71.1, U16.6
/X_SA_PD: Q8.3, R77.1, U16.9
/ZEROIZE_HW: J_HARN1.15, TP9.1
GND: C1.2, C2.2, C3.2, C4.2, C5.2, C6.2, C7.2, C8.2, C9.2, C10.2, C11.2, C12.2, C13.2, C14.2, C15.2, C16.2, C17.2, C18.2, C19.2, C20.2, C21.2, C22.2, C23.2, C24.2, C25.2, C26.2, C27.2, C29.2, C31.2, C32.2, C33.2, C37.2, C38.2, C39.2, C40.2, C44.2, C45.2, C49.2, C50.2, C51.2, C52.2, C53.2, C54.2, C55.2, C56.2, C57.2, C58.2, C59.2, C60.2, C61.2, C62.2, C63.2, D1.1, J_ANT.2, J_HARN1.3, J_HARN1.4, J_HARN1.5, J_HARN1.6, J_HARN1.14, J_HS1.2, J_HS1.4, J_HS2.2, J_HS2.4, J_PAIN.2, J_PAOUT.2, J_PWR1.2, J_USB3.4, J_VGG.2, LED1.1, LED4.1, LED5.1, Q1.2, Q2.2, R2.2, R3.2, R14.2, R15.2, R18.2, R19.2, R22.2, R23.2, R24.2, R25.2, R32.2, R34.2, R37.2, R39.2, R47.2, R53.2, R55.2, U1.2, U2.9, U2.10, U3.3, U3.29, U4.7, U4.8, U4.27, U4.28, U4.31, U5.2, U6.1, U6.6, U6.13, U6.20, U6.23, U6.24, U6.25, U6.28, U7.7, U7.10, U7.15, U7.17, U8.4, U9.3, U10.3, U11.3, U12.3, U13.3, U14.3, U15.4, U15.7, U16.12, U16.21, Y1.2, Y1.4, Y2.2, Y2.4
